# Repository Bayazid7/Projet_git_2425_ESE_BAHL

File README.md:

# Projet_git_2425_ESE
Projet_2024/2025
## Membres du groupes
Bayazid BELKHIR
<br>
Hedia WERHENI
<br>
Hugo DEVAUX
<br>
Aliou LY

## Introduction

Ce projet a pour objectif de développer un **robot autonome** utilisant un **microcontrôleur STM32** pour la gestion de son comportement, tout en appliquant des principes de noyaux **temps réel** pour contrôler la communication entre ses composants matériels et logiciels. Ce robot sera capable de fonctionner en deux modes :
- **Mode Chat** :
- **Mode Souris** :

Le robot est alimenté par une batterie de 7.2V et comprend des composants essentiels pour son fonctionnement tels que des moteurs, un accéléromètre, et un LIDAR.

---

## Objectifs du projet

Les principaux objectifs de ce projet sont les suivants :
1. **Conception du système à microcontrôleur STM32** : Intégrer un microcontrôleur  pour gérer le comportement du robot.
2. **Implémentation d'un noyau temps réel** : Utiliser un noyau temps réel pour garantir une gestion efficace des tâches .
3. **Contrôle des moteurs avec PWM** : Piloter deux moteurs à l'aide de drivers PWM pour contrôler la vitesse et la direction.
4. **Détection des chocs avec l'accéléromètre ADXL343** : Détecter les collisions avec d'autres robots pour ajuster les actions du robot.
5. **Détection des autres robots avec LIDAR YDLIDAR X4** : Utiliser un LIDAR pour permettre au robot de connaître la position des autres robots.

---

## Matériel utilisé

### 1. **Microcontrôleur STM32**

Le projet repose sur un **STM32** qui gère l'ensemble du système.La programmation du STM32 se fait par un SW

- **Modèle utilisé** : STM32G431CBU6
- **Fonction principale** : Gestion des moteurs, communication avec l'accéléromètre et le LIDAR, traitement des données en temps réel.
- **Peripherals** : PWM pour le contrôle des moteurs, interfaces I2C pour l'accéléromètre et UARTpour  le LIDAR et la communication avec le PC.

### 2. **Alimentation et régulation de tension**

Le robot est alimenté par une batterie **NIMH 7.2V 1.3Ah**. Cette tension est ensuite convertie en différentes tensions nécessaires au bon fonctionnement des différents composants :
- **Convertisseur 3.3V BU33SD5WG-TR** pour alimenter le STM32, l'accéléromètre, et les capteurs de position des moteurs.
- **Convertisseur 5V  MP1475S** pour alimenter le LIDAR.

---

### 3. **Drivers de moteurs PWM**

Le robot est équipé de **deux moteurs DC**, chacun étant contrôlé par un driver PWM. Chaque driver reçoit des signaux PWM du STM32 pour réguler la vitesse et la direction des moteurs.

- **Modèle des drivers** : ZXBM5210-SP-13
- **Fonction principale** : Piloter les moteurs en avant ou en arrière grâce à des signaux PWM.
- **Commandes PWM** : Les signaux PWM (Forward et Reverse) contrôlent la direction des moteurs. La vitesse est ajustée en modifiant le rapport cyclique du PWM.

### 4. **Accéléromètre ADXL343**

L'accéléromètre **ADXL343** est utilisé pour détecter les chocs entre les robots. Il mesure l'accélération dans les trois axes et peut détecter des variations rapides, comme celles d'une collision.

- **Communication** : Le module utilise le protocole **I2C** pour envoyer les données d'accélération au STM32.
- **Fonction principale** : Détecter les impacts ou les vibrations et permettre une réaction rapide du robot (comme changer de direction ou ajuster son comportement).

### 5. **LIDAR YDLIDAR X2**

Le **LIDAR YDLIDAR X4** est utilisé pour scanner l'environnement autour du robot et déterminer la position des autres robots et des obstacles. 
- **Type de capteur** : **LIDAR à balayage laser**.
- **Portée** : Jusqu'à 12 mètres.
- **Communication** : **UART**  pour transmettre les données de mesure.
- **Protocole**  : Utilise une communication série avec un format de trame spécifique (en-tête 0x55AA).
- **Résolution** : Distance : 0.25 mm (valeur brute divisée par 4) et Angle : 1/64° (0.015625°)

---
# Schema de cablage

## Software

### **Drivers de Moustache**
### **1. Fichier `Moustache.c`**-contient l'implémentation du pilote pour gérer les interruptions et les tâches liées à un système utilisant des capteurs "moustaches" pour détecter des bords.
**Principales fonctions et variables :
1. **Variables principales :**
   - `cb_out1_task_handle` et `cb_out2_task_handle` : Des handles pour les tâches FreeRTOS associées aux deux GPIO.
   - `exclusive_task` : Variable pour enregistrer quelle tâche est en cours d'exécution, afin d'éviter que plusieurs tâches ne soient actives simultanément ( On a remarqué que lorsque l'une des deux moustaches détecte le bord, la deuxième va également interrompre après un petit moment, et cela est dû à la conception du robot ). 
     - `0`: Aucune tâche active.
     - `1`: La tâche `CB_OUT1_Task` est active.
     - `2`: La tâche `CB_OUT2_Task` est active.
   - `robot` : Variable globale externe, représentant l'état d'un robot. Elle est utilisée dans la fonction `Bord`.

2. **Initialisation (`Moustache_Init`):**
   - Création de deux tâches FreeRTOS :
     - `CB_OUT1_Task` pour gérer les événements associés au GPIO `CB_OUT1_Pin`.
     - `CB_OUT2_Task` pour gérer les événements associés au GPIO `CB_OUT2_Pin`.

3. **Gestion des interruptions (`Moustache_HandleInterrupt`):**
   - Cette fonction est appelée lorsqu'une interruption GPIO est détectée.
   - Vérifie si une tâche peut être exécutée (selon la valeur de `exclusive_task`).
   - Envoie une notification à la tâche correspondante (`cb_out1_task_handle` ou `cb_out2_task_handle`) en utilisant `xTaskNotifyFromISR`.

4. **Fonction `Bord` :**
   - Gère le comportement du robot en fonction de sa direction (`robot.direction`).
     - `'A'`: Le robot recule.
     - `'R'`: Le robot avance.
   - Cette fonction est appelée par les tâches pour ajuster le mouvement du robot.

5. **Tâches `CB_OUT1_Task` et `CB_OUT2_Task` :**
   - Chaque tâche attend une notification via `xTaskNotifyWait`.
   - Lorsqu'une notification est reçue :
     - Elle effectue une action définie (appel de `Bord`).
     - Réinitialise `exclusive_task` à 0 pour permettre d'autres interruptions.

#### **2. Fichier `Moustache.h`**

Ce fichier est l'en-tête associé, qui déclare les prototypes des fonctions et les dépendances nécessaires.

#### **Principales fonctionnalités :**

1. **Inclusion de bibliothèques nécessaires :**
   - `stm32g4xx_hal.h` : Bibliothèque HAL pour la famille STM32G4.
   - `gpio.h` : Bibliothèque pour gérer les GPIO.

2. **Prototypes de fonctions :**
   - `Moustache_Init(void)` : Initialisation du pilote et des tâches.
   - `Moustache_HandleInterrupt(uint16_t GPIO_Pin)` : Gestion des interruptions GPIO.

___
### **Drivers de Moteur**

### 1.Fichier 'MoteurPWM.c' 

1. **La fonction Moteur_init:** 

Est responsable de l'initialisation d'un moteur en configurant ses paramètres de base. Elle prend en entrée un pointeur vers la structure du moteur, le timer PWM et le canal associé, initialisant la direction à l'arrêt et la vitesse à zéro.

2. **Moteur_setSpeed:**
gère la vitesse du moteur avec une conversion d'échelle, transformant une vitesse d'entrée (±290) en valeur PWM (0-8500) et configurant la direction appropriée.

3. **Moteur_setDirection:**

contrôle la direction du moteur en gérant les signaux PWM complémentaires elle peut faire avancer, reculer ou arrêter le moteur en activant ou désactivant les canaux PWM appropriés.

4. **Moteur_start, Moteur_stop et Moteur_recule:**

sont des fonctions d'aide qui simplifient le contrôle du moteur en appelant Moteur_setDirection avec les paramètres appropriés.

Du côté du robot, Robot_Start initialise le mouvement en avant avec des vitesses asymétriques (120 pour la droite, 80 pour la gauche), tandis que Robot_Stop arrête les deux moteurs.Robot_Recule fait reculer le robot avec les mêmes vitesses que l'avance mais en négatif.

## 2.Fichier 'MoteurPWM.h' 

c'est un fichier d’en-tête conçu pour gérer le contrôle des moteurs d’un robot. Il définit deux structures principales :

1. **Moteur_HandleTypeDef :** utilisée pour représenter un moteur individuel, incluant ses paramètres essentiels comme le timer PWM associé (pwm_timer), le canal PWM (channel), la direction actuelle (direction) et la vitesse (vitesse).
   
2. **h_Robot :** utilisée pour représenter un robot comprenant deux moteurs (droit et gauche) et des paramètres globaux comme la vitesse linéaire, la vitesse angulaire, l’angle (theta) et le mode de fonctionnement.

pour que en peux controlé l'angle de lidar nous allons utulisé La fonction : 
xTaskCreate(robotAngle, "Init Task", 256, NULL, 2, &setangleTaskHandle)  sert à créer une tâche dans un système RTOS. Cette tâche exécute la fonction robotAngle telque: 

utilise une pile de 256 mots, et a une priorité de 2. Le nom "Init Task" est utilisé pour identifier la tâche, et le handle setangleTaskHandle permet de la contrôler ultérieurement. Cette commande initialise efficacement la tâche pour qu'elle s'exécute dans le système.

## 4 .Driver ADXL343 (`ADXL343.c`)

## Introduction

Le driver **ADXL343** permet de gérer un accéléromètre **ADXL343** dans un système embarqué en temps réel. Ce capteur mesure l'accélération sur trois axes (X, Y, Z) et est utilisé pour détecter des événements comme les chocs. Ce driver est conçu pour intégrer les fonctionnalités du capteur avec **FreeRTOS**.

### 1. **Initialisation et Configuration du Capteur**

Le driver initialise le **capteur ADXL343** en configurant les registres nécessaires pour le fonctionnement de l'accéléromètre. Cela inclut la configuration de la plage de mesures, des seuils de tapotement, et des interruptions.

- **Initialisation de l'I2C** : La fonction `ADXL343_Init()` initialise la communication I2C avec le capteur, vérifie l'identifiant du dispositif et configure les registres pour la lecture des données d'accélération.
- **Configuration des Interrups** : Le capteur est configuré pour détecter des événements sur les axes X et Y, en activant les interruptions pour ces axes.
- **Configuration du Format des Données** : Le capteur est configuré pour un mode de résolution complète avec une plage de ±16g, ce qui est adapté pour de nombreuses applications.

### 2. **Réception et Traitement des Données**

Une fois l'accéléromètre configuré, le driver permet de récupérer les données d'accélération en temps réel.
- **Traitement des Interruptions** : Le driver utilise des interruptions pour détecter des événements de tapotement (tap) sur les axes X et Y.

### 3. **Gestion des Interruptions**

- **Gestion des Interruptions Tap** : Le capteur est configuré pour activer les interruptions uniquement pour les axes X et Y, en désactivant l'axe **Z** qui peut souvent générer des interruptions indésirables.
  
### 4. **Intégration en Temps Réel** ⏱️

- **Utilisation de FreeRTOS** : Le driver fonctionne avec **FreeRTOS** pour gérer les tâches liées à la lecture des données du capteur et au traitement des événements. Une tâche dédiée `TapDetectedTask` est utilisée pour traiter les événements en temps réel.

## 5. Drivers Ylidar X2 (`lidar_X2_driver.c`)

Le code du dirver implémente la gestion d'un capteur LiDAR YLIDAR X2 dans un système embarqué temps réel. Ci-dessous, les principaux aspects du fonctionnement du LiDAR :
### Initialisation et réception des données
La fonction `lidar_init()` initialise la communication UART avec le LiDAR en mode interruption. La réception des données se fait octet par octet via la fonction `readTrame()`, qui implémente une **machine à états** pour assembler les trames complètes.
### Traitement des données
Une fois une trame complète reçue, `lidar_process()` est appelée pour extraire et traiter les données :
- `lidar_extractDataFromTrame()` décode la structure de la trame.
- `lidar_DataProcessing()` calcule la distance et l'angle pour chaque point mesuré.
- `lidar_calculatingDistance()` et `lidar_calculatingAngle()` effectuent les calculs spécifiques.

### Intégration temps réel
- Utilisation d'interruptions UART pour la réception asynchrone des données.
- Traitement des données dans une tâche FreeRTOS dédiée (`lidarTask`).
- Synchronisation avec d'autres tâches du système pour le contrôle du robot.

### Pistes d'amélioration
- Implémenter la vérification du checksum pour valider l'intégrité des données.
- Optimiser le traitement des données pour réduire la charge CPU.
- Ajouter des filtres pour améliorer la précision des mesures.
- Implémenter une gestion d'erreurs plus robuste.

## Datasheets et sourcing des composants
https://1drv.ms/x/s!AjphXEW6glNckYErezblGW1QHlP9SQ

## Démonstrations du robot en marche:

https://github.com/user-attachments/assets/f6af12cb-7911-474c-adf0-7a1f33a06a41

https://github.com/user-attachments/assets/32c66e7f-6e20-4e83-ad37-8ae89d0b7e4e

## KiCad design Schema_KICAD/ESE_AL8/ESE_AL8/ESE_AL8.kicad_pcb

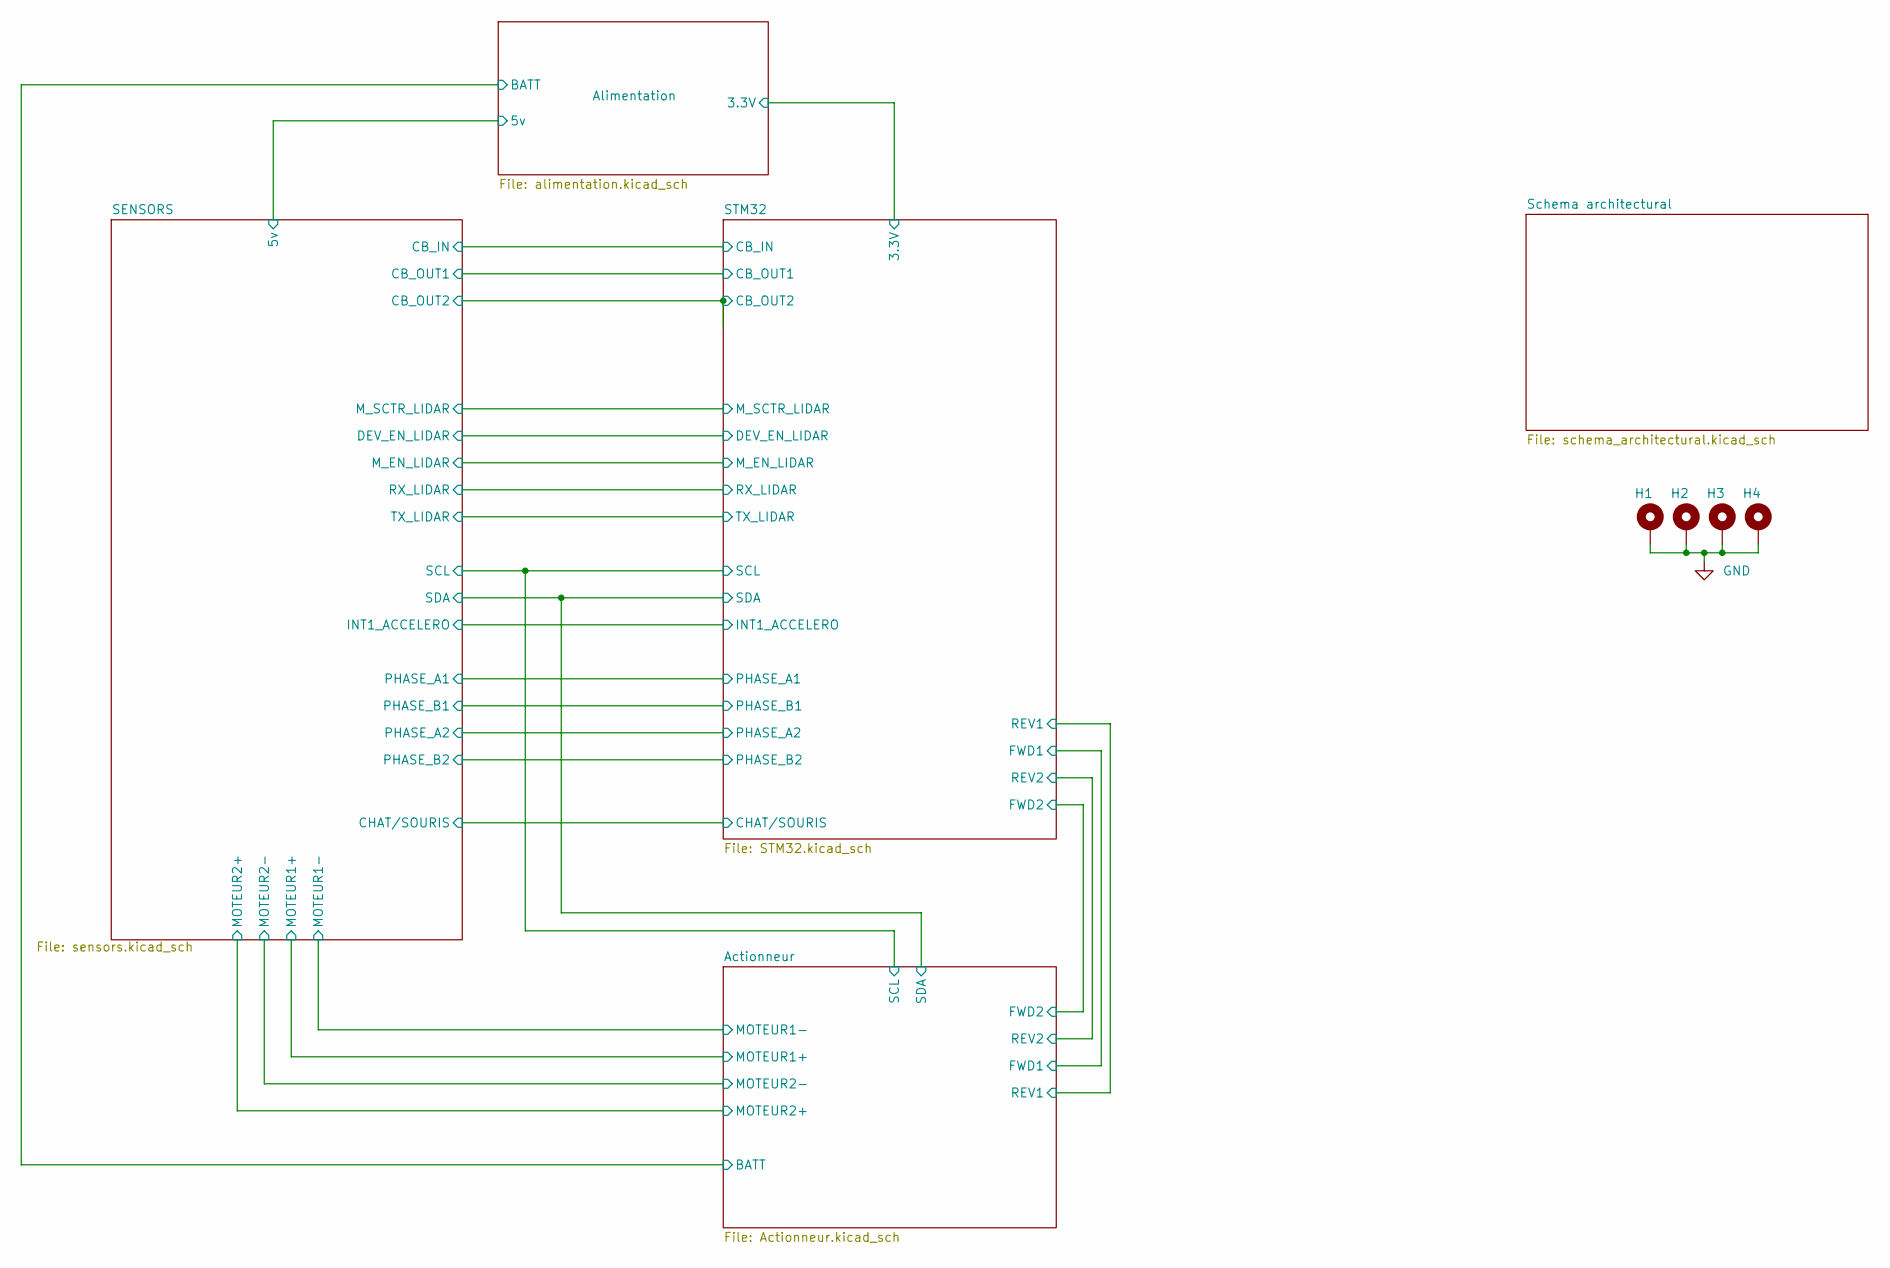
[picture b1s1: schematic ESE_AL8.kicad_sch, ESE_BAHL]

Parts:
H1, H2, H3, H4: MountingHole_Pad; MountingHole_3.2mm_M3_Pad_Via

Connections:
GND: H1.1, H2.1, H3.1, H4.1; also elsewhere on the board

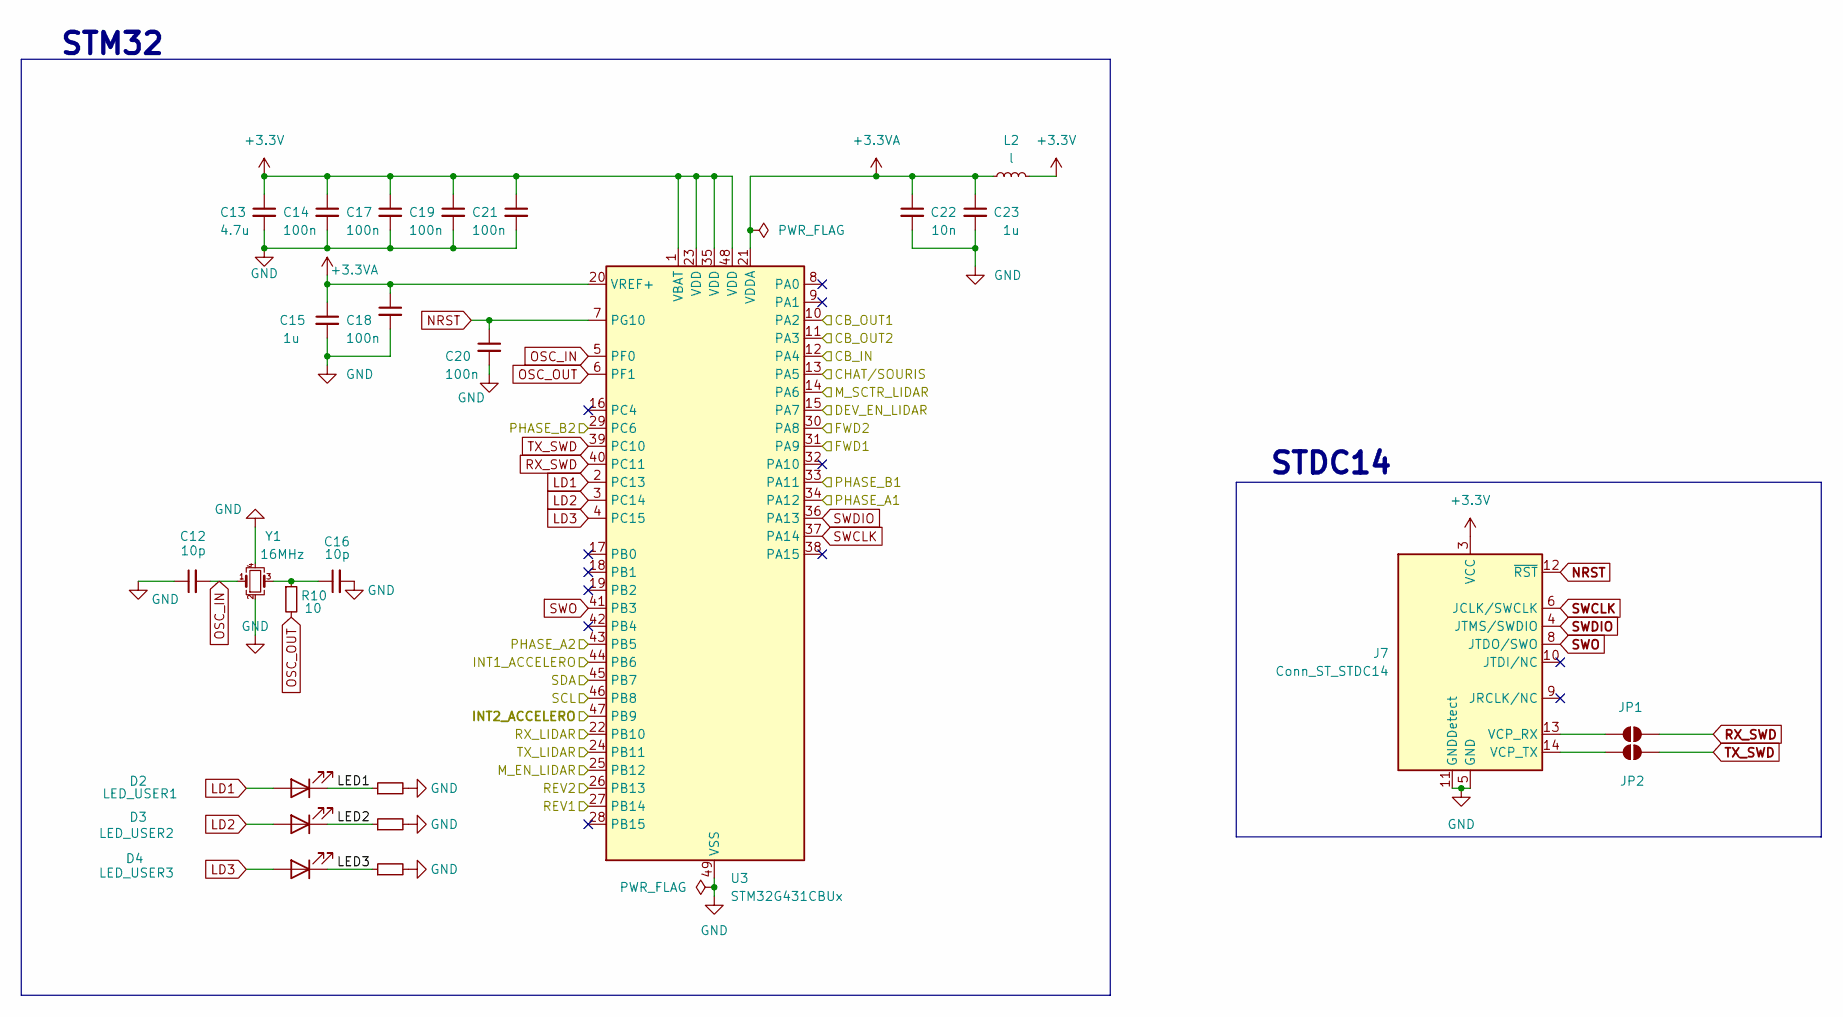
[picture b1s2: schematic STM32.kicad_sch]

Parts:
C12, C16: 10p; C_0402_1005Metric
C13: 4.7u; C_0603_1608Metric
C14, C17, C18, C19, C20, C21: 100n; C_0402_1005Metric
C15, C23: 1u; C_0603_1608Metric
C22: 10n; C_0402_1005Metric
D2: LED_USER1; LED_0603_1608Metric
D3: LED_USER2; LED_0603_1608Metric
D4: LED_USER3; LED_0603_1608Metric
J7: Conn_ST_STDC14; PinHeader_2x07_P1.27mm_Vertical_SMD
JP1, JP2: SolderJumper_2_Open; SolderJumper-2_P1.3mm_Open_RoundedPad1.0x1.5mm
L2: l; C_0402_1005Metric_Pad0.74x0.62mm_HandSolder
R10: 10; R_0402_1005Metric
R11, R12, R13: 680; R_0402_1005Metric
U3: STM32G431CBUx; QFN-48-1EP_7x7mm_P0.5mm_EP5.6x5.6mm_AJ
Y1: 16MHz; Crystal_SMD_3225-4Pin_3.2x2.5mm

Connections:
+3.3V: C13.1, C14.1, C17.1, C19.1, C21.1, J7.3 (VCC), L2.2, U3.1 (VBAT), U3.23 (VDD), U3.35 (VDD), U3.48 (VDD); also elsewhere on the board
+3.3VA: C15.1, C18.1, C22.1, C23.1, L2.1, U3.20 (VREF+), U3.21 (VDDA)
/Actionneur/FWD1: U3.31 (PA9); also elsewhere on the board
/Actionneur/FWD2: U3.30 (PA8); also elsewhere on the board
/Actionneur/REV1: U3.27 (PB14); also elsewhere on the board
/Actionneur/REV2: U3.26 (PB13); also elsewhere on the board
/Actionneur/SCL: U3.46 (PB8); also elsewhere on the board
/Actionneur/SDA: U3.45 (PB7); also elsewhere on the board
/SENSORS/CB_IN: U3.12 (PA4); also elsewhere on the board
/SENSORS/CB_OUT1: U3.10 (PA2); also elsewhere on the board
/SENSORS/CB_OUT2: U3.11 (PA3); also elsewhere on the board
/SENSORS/CHAT/SOURIS: U3.13 (PA5); also elsewhere on the board
/SENSORS/DEV_EN_LIDAR: U3.15 (PA7); also elsewhere on the board
/SENSORS/INT1_ACCELERO: U3.44 (PB6); also elsewhere on the board
/SENSORS/INT2_ACCELERO: U3.47 (PB9); also elsewhere on the board
/SENSORS/M_EN_LIDAR: U3.25 (PB12); also elsewhere on the board
/SENSORS/M_SCTR_LIDAR: U3.14 (PA6); also elsewhere on the board
/SENSORS/PHASE_A1: U3.34 (PA12); also elsewhere on the board
/SENSORS/PHASE_A2: U3.43 (PB5); also elsewhere on the board
/SENSORS/PHASE_B1: U3.33 (PA11); also elsewhere on the board
/SENSORS/PHASE_B2: U3.29 (PC6); also elsewhere on the board
/SENSORS/RX_LIDAR: U3.22 (PB10); also elsewhere on the board
/SENSORS/TX_LIDAR: U3.24 (PB11); also elsewhere on the board
/STM32/LED1: D2.1 (K), R11.1
/STM32/LED2: D3.1 (K), R12.1
/STM32/LED3: D4.1 (K), R13.1
GND: C12.1, C13.2, C14.2, C15.2, C16.2, C17.2, C18.2, C19.2, C20.2, C21.2, C22.2, C23.2, J7.5 (GND), J7.7 (GND), J7.11 (GNDDetect), R11.2, R12.2, R13.2, U3.49 (VSS), Y1.2, Y1.4; also elsewhere on the board
LD1: D2.2 (A), U3.2 (PC13)
LD2: D3.2 (A), U3.3 (PC14)
LD3: D4.2 (A), U3.4 (PC15)
NRST: C20.1, J7.12 (~RST), U3.7 (PG10)
unnamed: C16.1, R10.1, Y1.3
unnamed: J7.13 (VCP_RX), JP1.1 (A)
unnamed: J7.14 (VCP_TX), JP2.1 (A)
OSC_IN: C12.2, U3.5 (PF0), Y1.1
OSC_OUT: R10.2, U3.6 (PF1)
RX_SWD: JP1.2 (B), U3.40 (PC11)
SWCLK: J7.6 (JCLK/SWCLK), U3.37 (PA14)
SWDIO: J7.4 (JTMS/SWDIO), U3.36 (PA13)
SWO: J7.8 (JTDO/SWO), U3.41 (PB3)
TX_SWD: JP2.2 (B), U3.39 (PC10)

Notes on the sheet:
STDC14
STM32

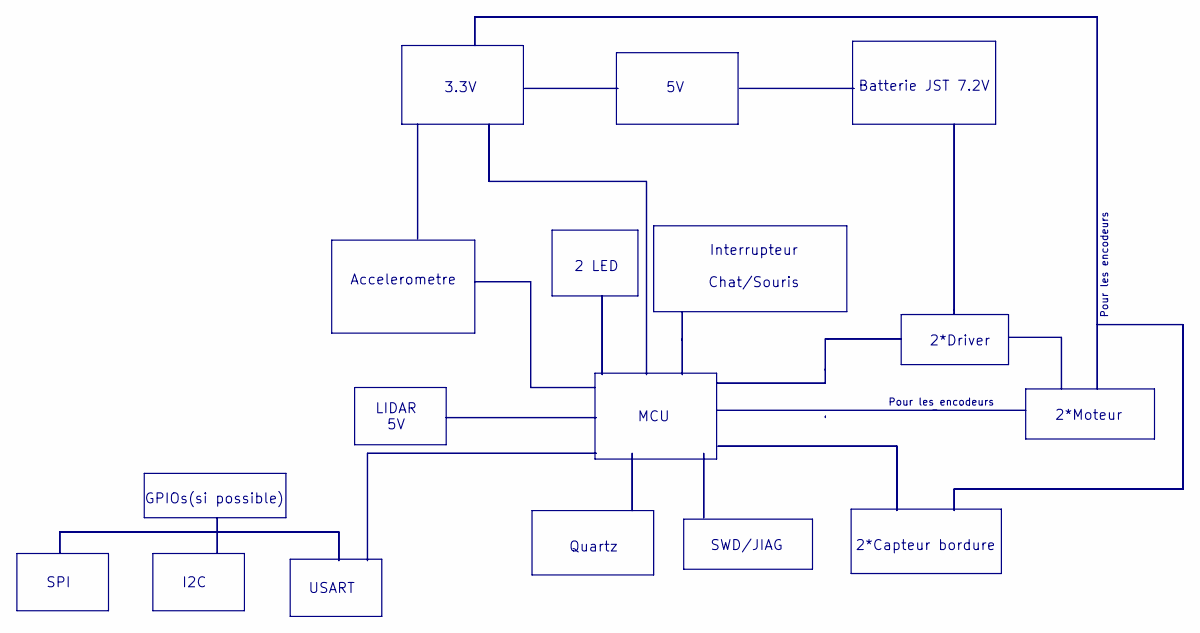
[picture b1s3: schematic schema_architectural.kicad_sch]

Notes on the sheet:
I2C
USART
2 LED
3.3V
Quartz
SWD/JIAG
SPI
GPIOs(si possible)
2*Moteur
Accelerometre
Interrupteur Chat/Souris
Pour les encodeurs
LIDAR 5V
Batterie JST 7.2V
2*Driver
2*Capteur bordure
MCU

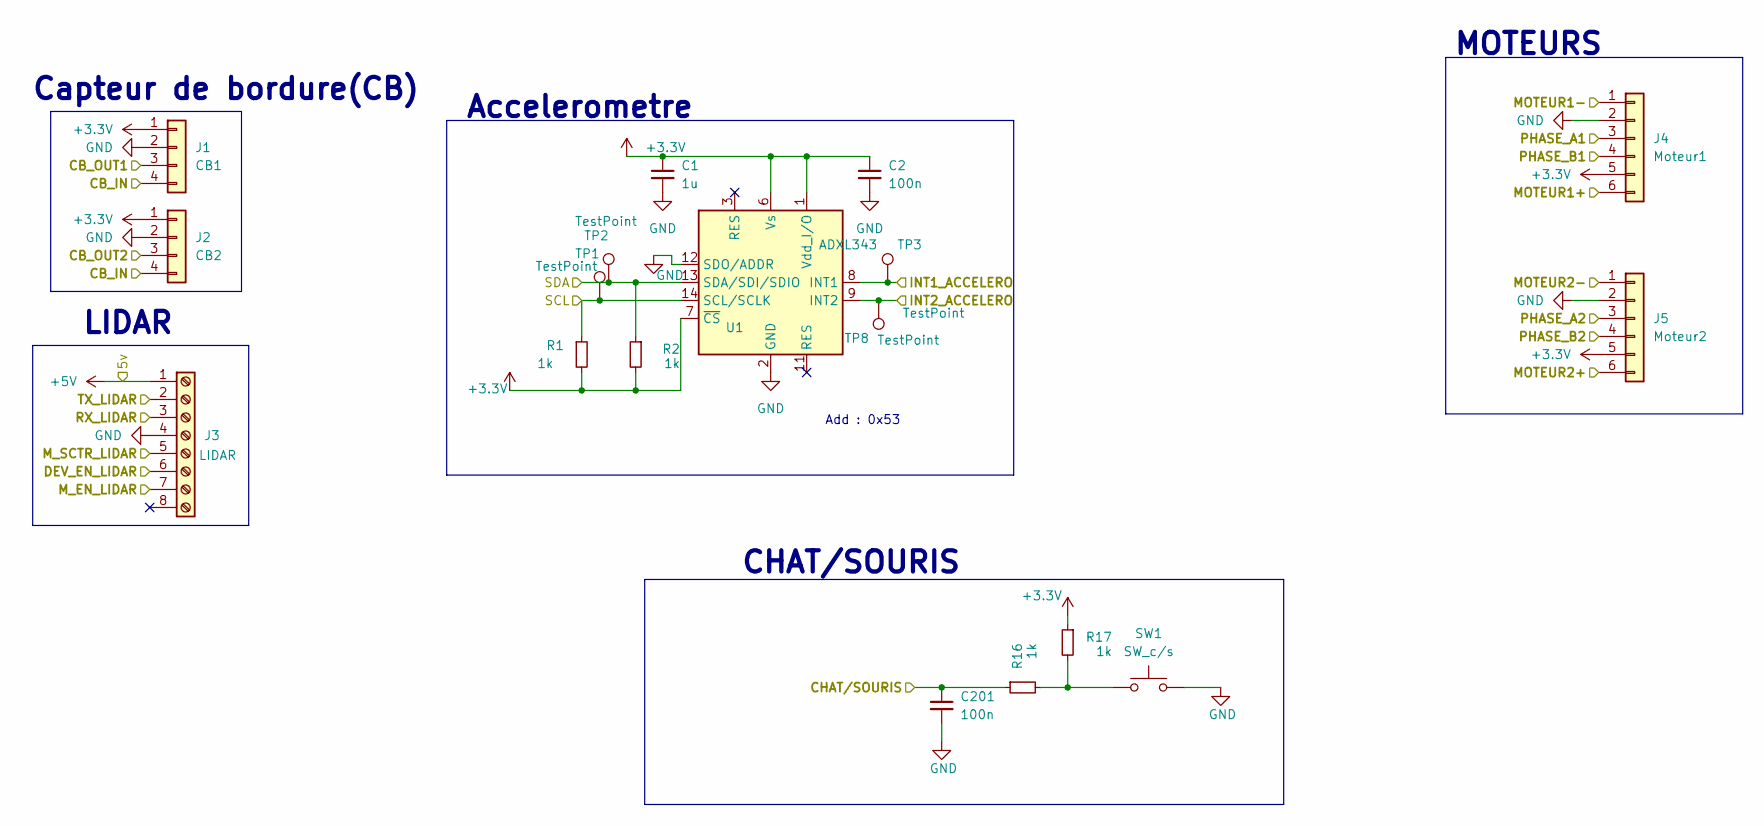
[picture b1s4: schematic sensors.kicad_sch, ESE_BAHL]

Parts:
C1: 1u; C_0603_1608Metric
C2, C201: 100n; C_0402_1005Metric
J1: CB1; JST_XH_S4B-XH-A_1x04_P2.50mm_Horizontal
J2: CB2; JST_XH_S4B-XH-A_1x04_P2.50mm_Horizontal
J3: LIDAR; JST_XH_S8B-XH-A_1x08_P2.50mm_Horizontal
J4: Moteur1; JST_XH_S6B-XH-A_1x06_P2.50mm_Horizontal
J5: Moteur2; JST_XH_S6B-XH-A_1x06_P2.50mm_Horizontal
R1, R2, R16, R17: 1k; R_0402_1005Metric
SW1: SW_c/s; SW_Push_1P1T_NO_6x6mm_H9.5mm
TP1, TP2, TP3, TP8: TestPoint; TestPoint_Pad_D1.0mm
U1: ADXL343; LGA-14_3x5mm_P0.8mm_LayoutBorder1x6y

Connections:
+3.3V: C1.1, C2.1, J1.1, J2.1, J4.5, J5.5, R1.2, R2.2, R17.1, U1.1 (Vdd_I/O), U1.6 (Vs), U1.7 (~CS); also elsewhere on the board
+5V: J3.1; also elsewhere on the board
/Actionneur/MOTEUR1+: J4.6; also elsewhere on the board
/Actionneur/MOTEUR1-: J4.1; also elsewhere on the board
/Actionneur/MOTEUR2+: J5.6; also elsewhere on the board
/Actionneur/MOTEUR2-: J5.1; also elsewhere on the board
/Actionneur/SCL: R1.1, TP1.1, U1.14 (SCL/SCLK); also elsewhere on the board
/Actionneur/SDA: R2.1, TP2.1, U1.13 (SDA/SDI/SDIO); also elsewhere on the board
/SENSORS/CB_IN: J1.4, J2.4; also elsewhere on the board
/SENSORS/CB_OUT1: J1.3; also elsewhere on the board
/SENSORS/CB_OUT2: J2.3; also elsewhere on the board
/SENSORS/CHAT/SOURIS: C201.1, R16.1; also elsewhere on the board
/SENSORS/DEV_EN_LIDAR: J3.6; also elsewhere on the board
/SENSORS/INT1_ACCELERO: TP3.1, U1.8 (INT1); also elsewhere on the board
/SENSORS/INT2_ACCELERO: TP8.1, U1.9 (INT2); also elsewhere on the board
/SENSORS/M_EN_LIDAR: J3.7; also elsewhere on the board
/SENSORS/M_SCTR_LIDAR: J3.5; also elsewhere on the board
/SENSORS/PHASE_A1: J4.3; also elsewhere on the board
/SENSORS/PHASE_A2: J5.3; also elsewhere on the board
/SENSORS/PHASE_B1: J4.4; also elsewhere on the board
/SENSORS/PHASE_B2: J5.4; also elsewhere on the board
/SENSORS/RX_LIDAR: J3.3; also elsewhere on the board
/SENSORS/TX_LIDAR: J3.2; also elsewhere on the board
GND: C1.2, C2.2, C201.2, J1.2, J2.2, J3.4, J4.2, J5.2, SW1.2, U1.2 (GND), U1.4 (GND), U1.5 (GND), U1.12 (SDO/ADDR); also elsewhere on the board
unnamed: R16.2, R17.2, SW1.1

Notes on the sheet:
LIDAR
MOTEURS
Accelerometre
Capteur de bordure(CB)
Add : 0x53
CHAT/SOURIS

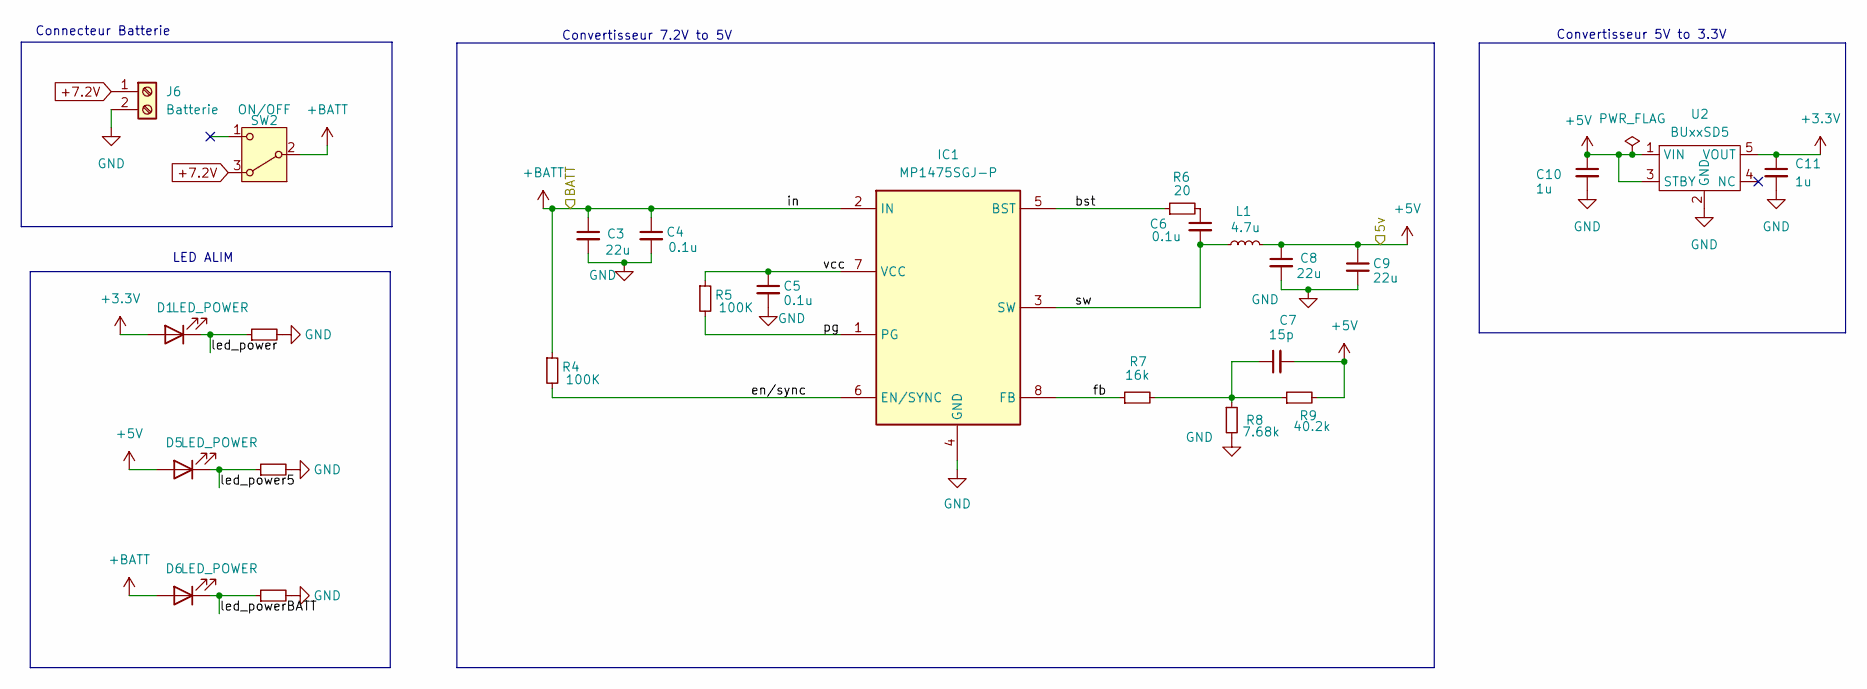
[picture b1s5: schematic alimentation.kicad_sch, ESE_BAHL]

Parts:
C3, C8, C9: 22u; C_0805_2012Metric
C4, C5, C6: 0.1u; C_0402_1005Metric
C7: 15p; C_0402_1005Metric
C10, C11: 1u; C_0603_1608Metric
D1, D5, D6: LED_POWER; LED_0603_1608Metric
IC1: MP1475SGJ-P; TSOT-23-8; Mouser Part Number 946-MP1475SGJ-P
J6: Batterie; JST_XH_S2B-XH-A_1x02_P2.50mm_Horizontal
L1: 4.7u; IND_052047_WRE
R3: 1k; R_0402_1005Metric
R4, R5: 100K; R_0402_1005Metric
R6: 20; R_0603_1608Metric
R7: 16k; R_0603_1608Metric
R8: 7.68k; R_0603_1608Metric
R9: 40.2k; R_0603_1608Metric
R14: 2.5; R_0402_1005Metric
R15: 4.2; R_0402_1005Metric
SW2: ON/OFF; JST_XH_S3B-XH-A_1x03_P2.50mm_Horizontal
U2: BUxxSD5; SOT-23-5

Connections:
+3.3V: C11.1, D1.2 (A), U2.5 (VOUT); also elsewhere on the board
+5V: C7.2, C8.1, C9.1, C10.1, D5.2 (A), L1.2, R9.2, U2.1 (VIN), U2.3 (STBY); also elsewhere on the board
+7.2V: J6.1, SW2.3 (A)
+BATT: C3.1, C4.1, D6.2 (A), IC1.2 (IN), R4.1, SW2.2 (B); also elsewhere on the board
/Alimentation/bst: IC1.5 (BST), R6.1
/Alimentation/en/sync: IC1.6 (EN/SYNC), R4.2
/Alimentation/fb: IC1.8 (FB), R7.1
/Alimentation/led_power: D1.1 (K), R3.1
/Alimentation/led_power5: D5.1 (K), R14.1
/Alimentation/led_powerBATT: D6.1 (K), R15.1
/Alimentation/pg: IC1.1 (PG), R5.2
/Alimentation/sw: C6.2, IC1.3 (SW), L1.1
/Alimentation/vcc: C5.1, IC1.7 (VCC), R5.1
GND: C3.2, C4.2, C5.2, C8.2, C9.2, C10.2, C11.2, IC1.4 (GND), J6.2, R3.2, R8.2, R14.2, R15.2, U2.2 (GND); also elsewhere on the board
unnamed: C6.1, R6.2
unnamed: C7.1, R7.2, R8.1, R9.1

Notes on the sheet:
Convertisseur 5V to 3.3V
LED ALIM
Convertisseur 7.2V to 5V
Connecteur Batterie

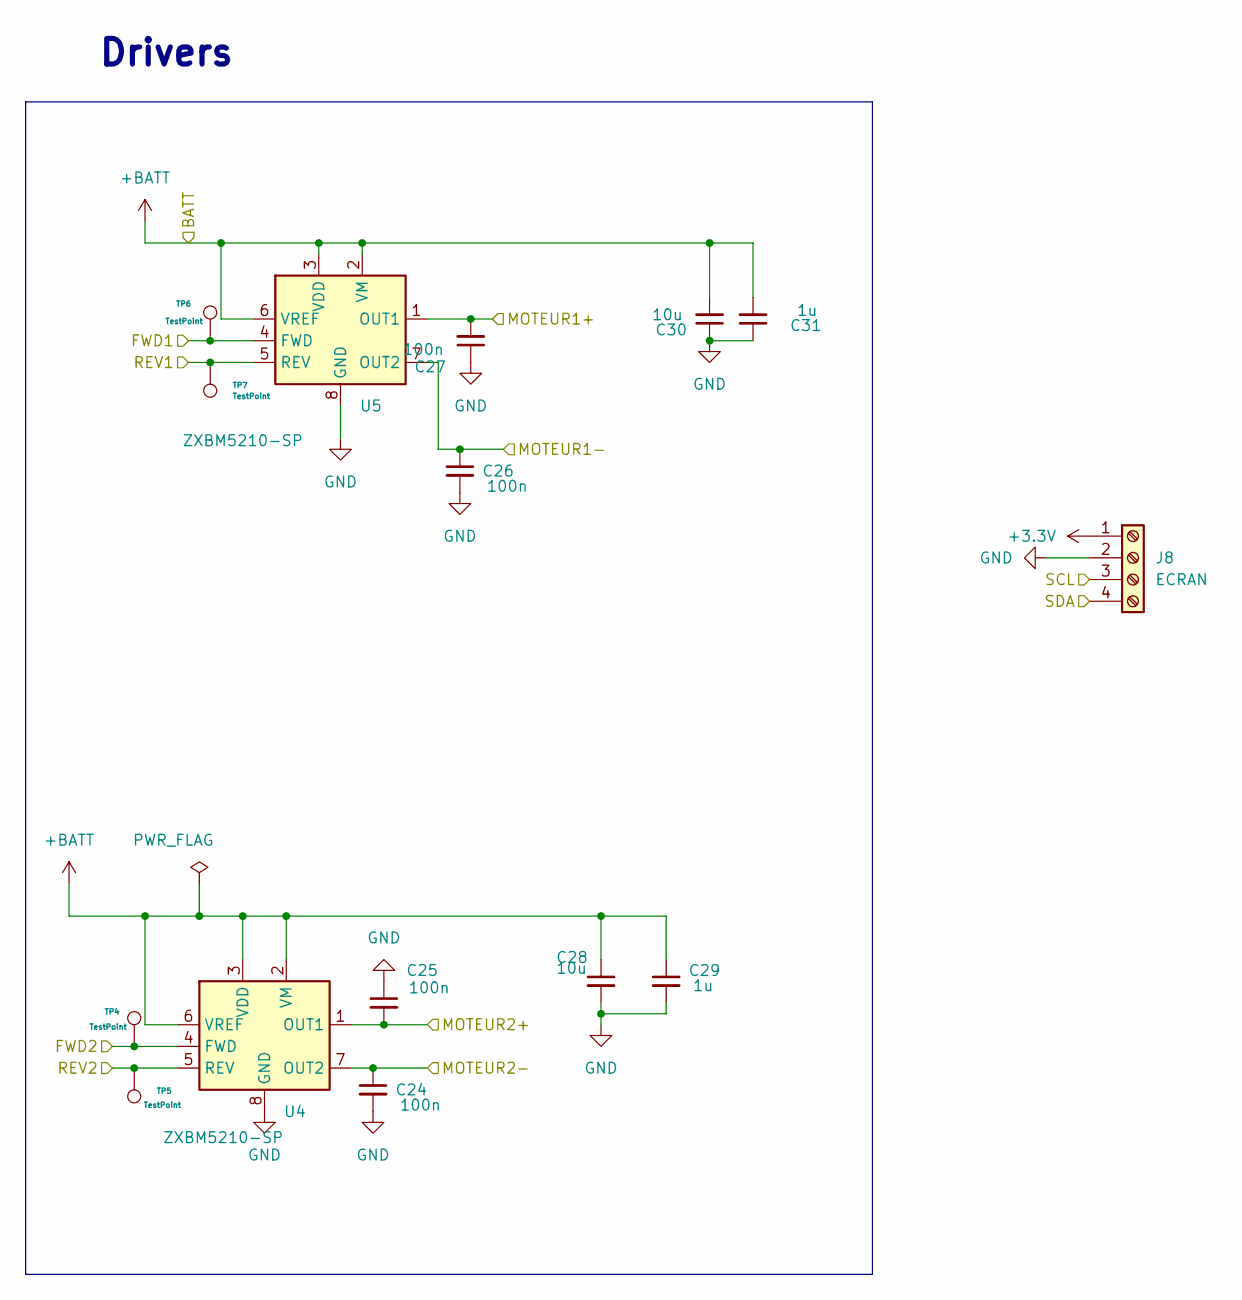
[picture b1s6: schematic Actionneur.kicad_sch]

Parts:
C24, C25, C26, C27: 100n; C_0402_1005Metric
C28, C30: 10u; C_0603_1608Metric
C29, C31: 1u; C_0603_1608Metric
J8: ECRAN; JST_XH_S4B-XH-A_1x04_P2.50mm_Horizontal
TP4, TP5, TP6, TP7: TestPoint; TestPoint_Pad_D1.0mm
U4, U5: ZXBM5210-SP; Diodes_SO-8EP

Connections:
+3.3V: J8.1; also elsewhere on the board
+BATT: C28.1, C29.1, C30.2, C31.2, U4.2 (VM), U4.3 (VDD), U4.6 (VREF), U5.2 (VM), U5.3 (VDD), U5.6 (VREF); also elsewhere on the board
/Actionneur/FWD1: TP6.1, U5.4 (FWD); also elsewhere on the board
/Actionneur/FWD2: TP4.1, U4.4 (FWD); also elsewhere on the board
/Actionneur/MOTEUR1+: C27.2, U5.1 (OUT1); also elsewhere on the board
/Actionneur/MOTEUR1-: C26.1, U5.7 (OUT2); also elsewhere on the board
/Actionneur/MOTEUR2+: C25.2, U4.1 (OUT1); also elsewhere on the board
/Actionneur/MOTEUR2-: C24.1, U4.7 (OUT2); also elsewhere on the board
/Actionneur/REV1: TP7.1, U5.5 (REV); also elsewhere on the board
/Actionneur/REV2: TP5.1, U4.5 (REV); also elsewhere on the board
/Actionneur/SCL: J8.3; also elsewhere on the board
/Actionneur/SDA: J8.4; also elsewhere on the board
GND: C24.2, C25.1, C26.2, C27.1, C28.2, C29.2, C30.1, C31.1, J8.2, U4.8 (GND), U4.9 (GND), U5.8 (GND), U5.9 (GND); also elsewhere on the board

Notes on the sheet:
Drivers

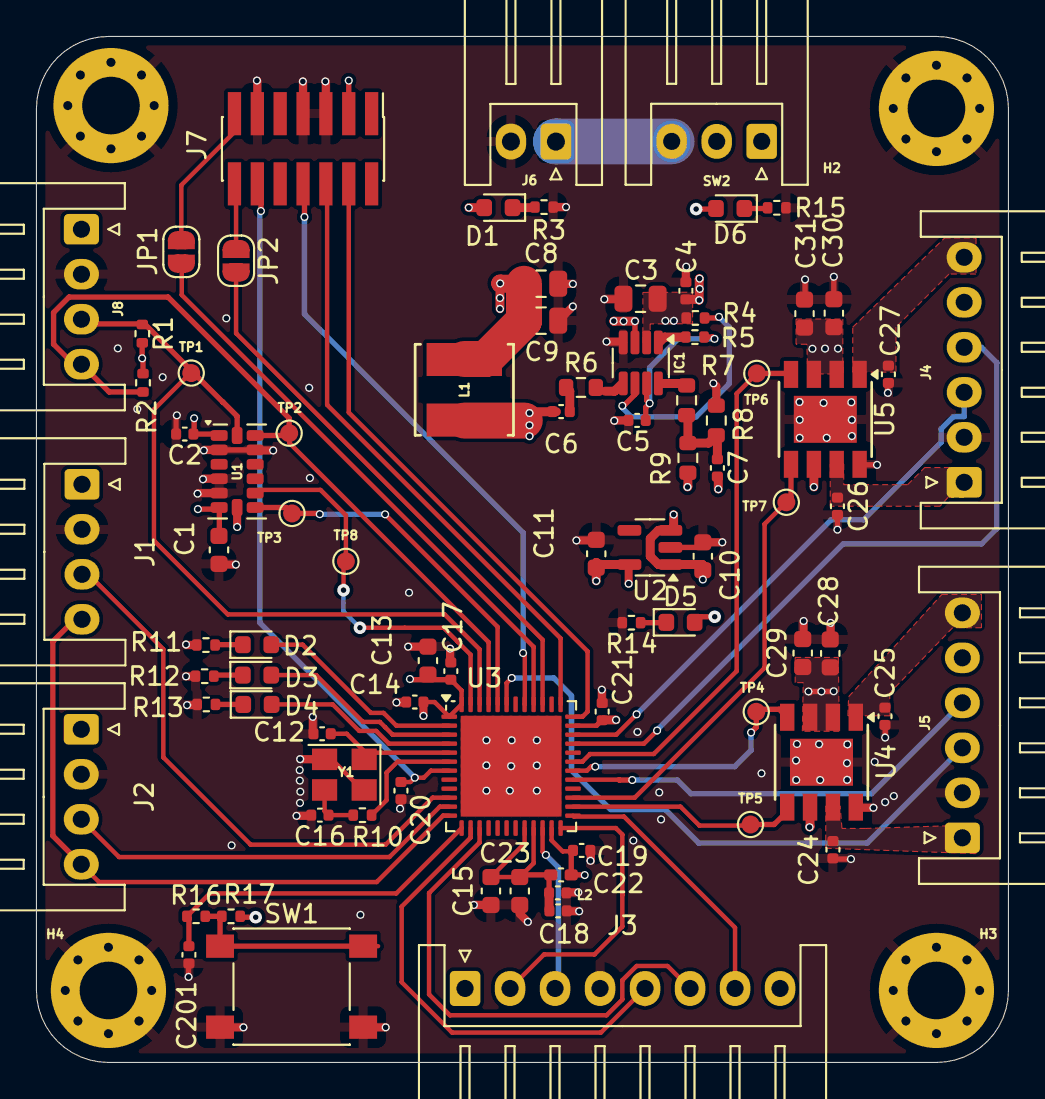
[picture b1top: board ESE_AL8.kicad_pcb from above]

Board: 4 copper layers, 54.0 x 57.0 mm, 88 parts (0 on the bottom side), 60 nets.

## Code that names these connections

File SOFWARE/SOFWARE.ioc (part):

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Mcu.Name=STM32G431C(6-8-B)Ux
Mcu.Package=UFQFPN48
Mcu.UserName=STM32G431CBUx
PA13.GPIOParameters=GPIO_Label
PA13.GPIO_Label=SWDIO
PA13.Mode=Trace_Asynchronous_SW
PA13.Signal=SYS_JTMS-SWDIO
PA14.GPIOParameters=GPIO_Label
PA14.GPIO_Label=SWCLK
PA14.Mode=Trace_Asynchronous_SW
PA14.Signal=SYS_JTCK-SWCLK
PA2.GPIOParameters=GPIO_Label,GPIO_ModeDefaultEXTI
PA2.GPIO_Label=CB_OUT1
PA2.GPIO_ModeDefaultEXTI=GPIO_MODE_IT_FALLING
PA2.Signal=GPXTI2
PA3.GPIOParameters=GPIO_Label,GPIO_ModeDefaultEXTI
PA3.GPIO_Label=CB_OUT2
PA3.GPIO_ModeDefaultEXTI=GPIO_MODE_IT_FALLING
PA3.Signal=GPXTI3
PA4.GPIOParameters=GPIO_Label
PA4.GPIO_Label=CB_IN
PA4.Signal=GPIO_Output
PA5.GPIOParameters=GPIO_Label,GPIO_ModeDefaultEXTI
PA5.GPIO_Label=CHAT/SOURIS
PA5.GPIO_ModeDefaultEXTI=GPIO_MODE_IT_FALLING
PA5.Signal=GPXTI5
PA6.GPIOParameters=GPIO_Label
PA6.GPIO_Label=M_SCTR_LIDAR
PA6.Signal=S_TIM16_CH1
PA7.GPIOParameters=GPIO_Label
PA7.GPIO_Label=DEV_EN_LIDAR
PA7.Signal=GPIO_Output
PA8.GPIOParameters=GPIO_ModeDefaultPP,GPIO_Speed,GPIO_PuPd
PA8.GPIO_ModeDefaultPP=GPIO_MODE_AF_PP
PA8.GPIO_PuPd=GPIO_NOPULL
PA8.GPIO_Speed=GPIO_SPEED_FREQ_LOW
PA8.Signal=S_TIM1_CH1
PA9.GPIOParameters=GPIO_ModeDefaultPP,GPIO_Speed,GPIO_PuPd
PA9.GPIO_ModeDefaultPP=GPIO_MODE_AF_PP
PA9.GPIO_PuPd=GPIO_NOPULL
PA9.GPIO_Speed=GPIO_SPEED_FREQ_LOW
PA9.Signal=S_TIM1_CH2
PB10.GPIOParameters=GPIO_Label
PB10.GPIO_Label=LIDAR_RX
PB10.Mode=Asynchronous
PB10.Signal=USART3_TX
PB11.GPIOParameters=GPIO_Label
PB11.GPIO_Label=LIDAR_TX
PB11.Mode=Asynchronous
PB11.Signal=USART3_RX
PB12.GPIOParameters=GPIO_Label
PB12.GPIO_Label=M_EN_LIDAR
PB12.Signal=GPIO_Output
PB13.GPIOParameters=GPIO_ModeDefaultPP,GPIO_Speed,GPIO_PuPd
PB13.GPIO_ModeDefaultPP=GPIO_MODE_AF_PP
PB13.GPIO_PuPd=GPIO_NOPULL
PB13.GPIO_Speed=GPIO_SPEED_FREQ_LOW
PB13.Mode=PWM Generation1 CH1 CH1N
PB13.Signal=TIM1_CH1N
PB14.GPIOParameters=GPIO_ModeDefaultPP,GPIO_Speed,GPIO_PuPd
PB14.GPIO_ModeDefaultPP=GPIO_MODE_AF_PP
PB14.GPIO_PuPd=GPIO_NOPULL
PB14.GPIO_Speed=GPIO_SPEED_FREQ_LOW
PB14.Mode=PWM Generation2 CH2 CH2N
PB14.Signal=TIM1_CH2N
PB3.GPIOParameters=GPIO_Label
PB3.GPIO_Label=SWO
PB3.Mode=Trace_Asynchronous_SW
PB3.Signal=SYS_JTDO-SWO
PB7.Mode=I2C
PB7.Signal=I2C1_SDA
PB8-BOOT0.Mode=I2C
PB8-BOOT0.Signal=I2C1_SCL
PB9.GPIOParameters=GPIO_Label,GPIO_ModeDefaultEXTI
PB9.GPIO_Label=INT2
PB9.GPIO_ModeDefaultEXTI=GPIO_MODE_IT_RISING
PB9.Signal=GPXTI9
PC10.GPIOParameters=GPIO_Label
PC10.GPIO_Label=TX_SWD
PC10.Mode=Asynchronous
PC10.Signal=UART4_TX
PC11.GPIOParameters=GPIO_Label
PC11.GPIO_Label=RX_SWD
PC11.Mode=Asynchronous
PC11.Signal=UART4_RX
PC13.GPIOParameters=GPIO_Label
PC13.GPIO_Label=LED1
PC13.Signal=GPIO_Output
PC14-OSC32_IN.GPIOParameters=GPIO_Label
PC14-OSC32_IN.GPIO_Label=LED2
PC14-OSC32_IN.Signal=GPIO_Output
PC15-OSC32_OUT.GPIOParameters=GPIO_Label
PC15-OSC32_OUT.GPIO_Label=LED3
PC15-OSC32_OUT.Signal=GPIO_Output
PF0-OSC_IN.Mode=HSE-External-Oscillator
PF0-OSC_IN.Signal=RCC_OSC_IN
PF1-OSC_OUT.Mode=HSE-External-Oscillator
PF1-OSC_OUT.Signal=RCC_OSC_OUT
RCC.HSE_VALUE=16000000
RCC.SYSCLKFreq_VALUE=170000000
RCC.SYSCLKSource=RCC_SYSCLKSOURCE_PLLCLK
board=custom

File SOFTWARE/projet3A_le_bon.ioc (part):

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Mcu.Name=STM32G431C(6-8-B)Ux
Mcu.Package=UFQFPN48
Mcu.UserName=STM32G431CBUx
PA0.GPIOParameters=GPIO_Label
PA0.GPIO_Label=DEV_EN
PA0.Signal=GPIO_Output
PA1.GPIOParameters=GPIO_Label
PA1.GPIO_Label=M_EN
PA1.Signal=GPIO_Output
PA10.GPIOParameters=GPIO_Label
PA10.GPIO_Label=M_SCTR_LIDAR
PA10.Signal=S_TIM1_CH3
PA11.GPIOParameters=GPIO_Label
PA11.GPIO_Label=ENCODER_A2
PA11.Signal=S_TIM4_CH1
PA12.GPIOParameters=GPIO_Label
PA12.GPIO_Label=ENCODER_B2
PA12.Signal=S_TIM4_CH2
PA13.Mode=Trace_Asynchronous_SW
PA13.Signal=SYS_JTMS-SWDIO
PA14.Mode=Trace_Asynchronous_SW
PA14.Signal=SYS_JTCK-SWCLK
PA2.GPIOParameters=GPIO_Label
PA2.GPIO_Label=TX_LIDAR
PA2.Mode=Asynchronous
PA2.Signal=USART2_TX
PA3.GPIOParameters=GPIO_Label
PA3.GPIO_Label=RX_LIDAR
PA3.Mode=Asynchronous
PA3.Signal=USART2_RX
PA5.GPIOParameters=GPIO_Label
PA5.GPIO_Label=CB_IN
PA5.Signal=GPIO_Output
PA6.GPIOParameters=GPIO_Label
PA6.GPIO_Label=CB_OUT1
PA6.Mode=IN3-Single-Ended
PA6.Signal=ADC2_IN3
PA7.GPIOParameters=GPIO_Label
PA7.GPIO_Label=CB_OUT2
PA7.Mode=IN4-Single-Ended
PA7.Signal=ADC2_IN4
PA8.GPIOParameters=GPIO_Label
PA8.GPIO_Label=FWD2
PA8.Signal=S_TIM1_CH1
PA9.GPIOParameters=GPIO_Label
PA9.GPIO_Label=FWD1
PA9.Signal=S_TIM1_CH2
PB0.GPIOParameters=GPIO_Label
PB0.GPIO_Label=CB_OUT4
PB0.Mode=IN15-Single-Ended
PB0.Signal=ADC1_IN15
PB1.GPIOParameters=GPIO_Label
PB1.GPIO_Label=CHAT/SOURIS
PB1.Signal=GPIO_Input
PB13.GPIOParameters=GPIO_Label
PB13.GPIO_Label=REV2
PB13.Mode=PWM Generation1 CH1 CH1N
PB13.Signal=TIM1_CH1N
PB14.GPIOParameters=GPIO_Label
PB14.GPIO_Label=REV1
PB14.Mode=PWM Generation2 CH2 CH2N
PB14.Signal=TIM1_CH2N
PB3.Mode=Trace_Asynchronous_SW
PB3.Signal=SYS_JTDO-SWO
PB5.GPIOParameters=GPIO_Label
PB5.GPIO_Label=ENCODER_B1
PB5.Signal=S_TIM3_CH2
PB6.GPIOParameters=GPIO_Label
PB6.GPIO_Label=INT_ACCELERO
PB6.Signal=GPIO_Input
PB7.Mode=I2C
PB7.Signal=I2C1_SDA
PB8-BOOT0.Mode=I2C
PB8-BOOT0.Signal=I2C1_SCL
PC10.GPIOParameters=GPIO_Label
PC10.GPIO_Label=SWD_TX
PC10.Mode=Asynchronous
PC10.Signal=USART3_TX
PC11.GPIOParameters=GPIO_Label
PC11.GPIO_Label=SWD_RX
PC11.Mode=Asynchronous
PC11.Signal=USART3_RX
PC13.GPIOParameters=GPIO_Label
PC13.GPIO_Label=LED1
PC13.Signal=GPIO_Output
PC14-OSC32_IN.Signal=GPIO_Output
PC15-OSC32_OUT.Signal=GPIO_Output
PC4.GPIOParameters=GPIO_Label
PC4.GPIO_Label=CB_OUT3
PC4.Mode=IN5-Single-Ended
PC4.Signal=ADC2_IN5
PC6.GPIOParameters=GPIO_Label
PC6.GPIO_Label=ENCODER_A1
PC6.Signal=S_TIM3_CH1
PF0-OSC_IN.Mode=HSE-External-Oscillator
PF0-OSC_IN.Signal=RCC_OSC_IN
PF1-OSC_OUT.Mode=HSE-External-Oscillator
PF1-OSC_OUT.Signal=RCC_OSC_OUT
RCC.HSE_VALUE=16000000
RCC.SYSCLKFreq_VALUE=170000000
RCC.SYSCLKSource=RCC_SYSCLKSOURCE_PLLCLK
board=custom

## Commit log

2024-09-11 Pour le schema_archi
2024-09-18 commit 18/09/202
2024-09-18 schema_architectural
2024-09-18 commit pour 18/09
2024-09-18 schema
2024-09-18 commit 1
2024-09-18 commit 18/09/24 18:10
2024-09-25 LE 25 /09/2024 10:31
2024-09-25 test
2024-09-25 commit 3
2024-09-25 commit AL08_1
2024-10-01 documents
2024-10-01 init branch testing
2024-10-01 commit du code et kicad modifié
2024-10-01 commit pour le schema
2024-10-01 kicad updated
2024-10-01 kicad delete
2024-10-02 commit pour le schema avec 2 CB
2024-10-02 .gitignore
2024-10-02 init commit dev_lidar -b
2024-10-02 commit pour le placement des composants 12h
2024-10-08 commit pour le schema aprés routage
2024-10-10 Routage aprés correction
2024-10-16 DriverSTM
2024-10-16 activationmoteurDC
2024-10-16 info drive.md
2024-10-16 Informations sur le drive moteur.md
2024-10-19 Rooting
2024-10-22 Informations sur le timer 3 de l'encodeur.
2024-10-22 Encodeur
2024-10-22 Commit midif pcb 2020
2024-10-22 Commit midif pcb 2207
2024-10-23 Commit midif pcb 23/10 0816
2024-10-23 Commit midif pcb 23/10 0914
2024-10-23 Commit midif pcb 23/10 0916
2024-10-23 Commit last modif 23/10/24 11:05
2024-10-23 Commit last modif 23/10/24 11:29
2024-10-23 drive+encodeur+pid
2024-11-13 Vitesse
2024-11-19 le bon ioc
2024-11-19 init
2024-11-26 push 26/11
2024-11-28 commit 28/11/24
2024-12-31 Moteur
2024-12-31 MoteurTask
2025-01-01 moustache
2025-01-04 commit merge 1
2025-01-06 commit 06/06/2021 23:34
2025-01-07 modif fonctionnel
2025-01-09 new version
2025-01-15 last
2025-01-15 Update README.md (videos)
